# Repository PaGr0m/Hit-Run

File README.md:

# Hit&Run

## Projects
* [Controller] --- устройство-приемник, обрабатывает приходящие сигналы, визуализирует фиксацию, оснащен таймером.
* [WeaponSender] --- устройство-передатчик, фиксирует нажатие механической кнопки на наконечнике оружия и посылает сигнал на приемник.
* [RadioRemoteControl] --- пульт ДУ, для усправления контроллером.

[Controller]: <https://github.com/PaGr0m/Hit-Run/tree/master/Controller>
[WeaponSender]: <https://github.com/PaGr0m/Hit-Run/tree/master/WeaponSender>
[RadioRemoteControl]: <https://github.com/PaGr0m/Hit-Run/tree/master/RadioRemoteControl>

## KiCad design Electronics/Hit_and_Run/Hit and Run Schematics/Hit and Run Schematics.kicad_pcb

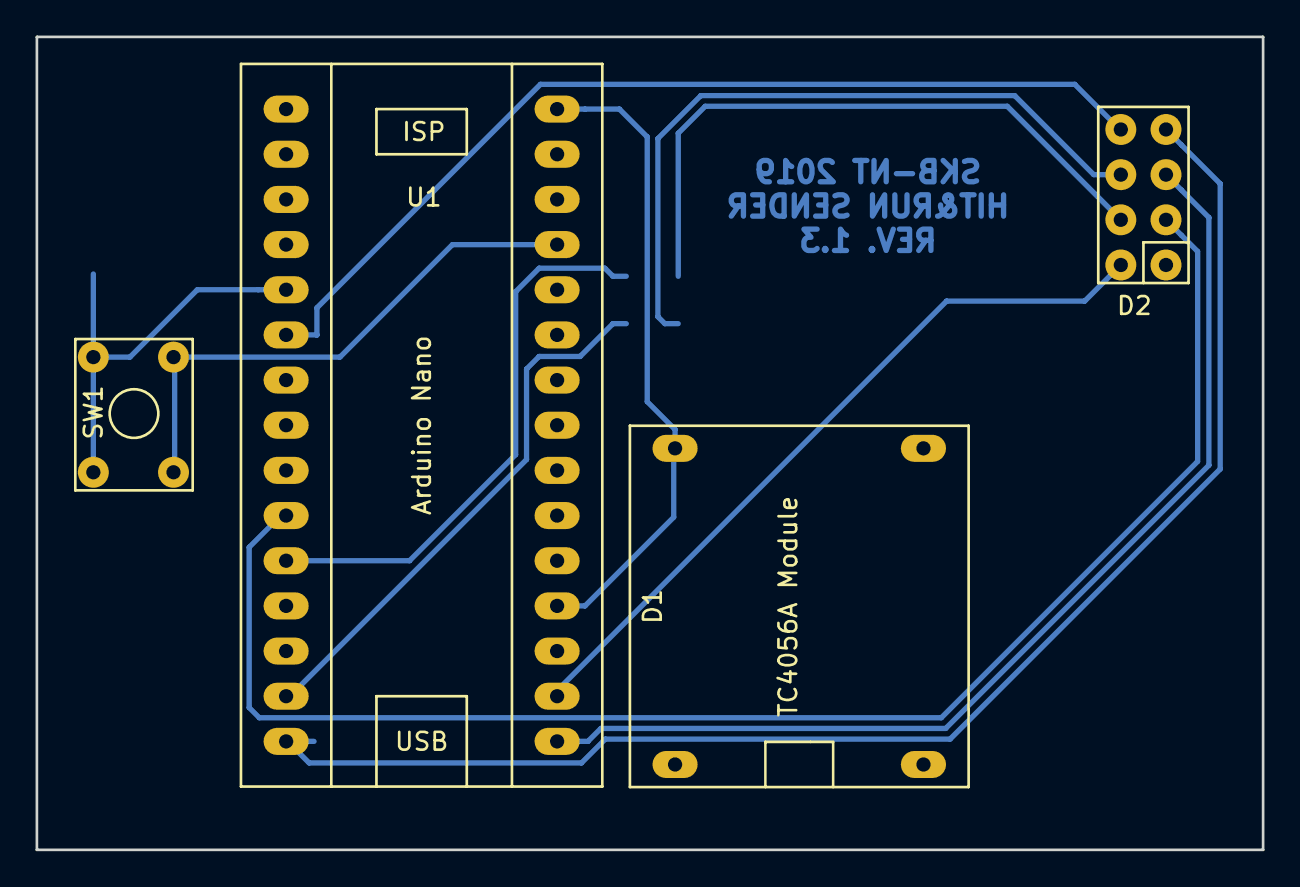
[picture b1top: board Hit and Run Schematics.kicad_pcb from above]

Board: 2 copper layers, 69.0 x 45.7 mm, 5 parts (0 on the bottom side), 11 nets.

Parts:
D1: TC4056A Module; TC4056A_Battery_module
D2: nRF24L01
R1: Default_Resistor; SMD_Resistor_1206
SW1: THT_Tactical_Button_6x6x3.5mm; THT_Tactical_Switch_6x6x3.5
U1: Arduino_Nano

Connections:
+3V3: D2.8, U1.17
+5V: SW1.2, U1.27
+BATT: D1.4, U1.19, U1.30
-BATT: D1.3, D2.1, R1.1, U1.29
unnamed: D2.2, U1.10
unnamed: D2.3, U1.16
unnamed: D2.4, U1.15
unnamed: D2.5, U1.6
unnamed: D2.6, U1.14
unnamed: D2.7, U1.11
unnamed: R1.2, SW1.1, U1.5

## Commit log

2019-02-14 Add some files
    Just program epee button. Test RF24 connection
2019-02-18 Separate Sender and Receiver
2019-02-19 Add Buzzer, Light-emitting diode
2019-02-20 Test SenderX2
2019-02-21 Complete Sender X2. Add Liquid Display
2019-02-25 Try RTC module
2019-02-25 Anything binary code
2019-04-16 Test code
2019-05-13 Working state
2019-05-14 Project Reborn
2019-05-15 Sender + Receiver + Controller
2019-05-17 IR remote control
2019-05-29 Test Interrupt NRF
2019-06-02 Test 2
2019-06-02 Test 3
2019-06-02 Hit&Run | Version 2.1
2019-06-03 Cleaning
2019-06-03 Cleaning
    Delete extra files
2019-06-03 Update .gitignore and delete extra files
2019-06-04 Test RadioRemoteControl
    Тестирование фичи. Следует проверить работоспособность на 2 Sender'ах, подумать о переделывании прерывания
2019-06-05 Rework RadioRemoteControl. Add comments in WeaponSender
2019-06-05 Add RTC timer, complete RadioRemoteControl
2019-06-06 Upd readme
2019-06-10 Add logger, delete ex files
2019-06-18 Upd SKB image
2019-06-18 Upd readme | Add skb link
2019-06-24 Little change
2019-06-24 Added LED Matrix and Buzzer.
    Added serialSettings. Rework comments. Added extra features
2019-06-24 Revert "Feature/led matrix"
2019-06-24 Revert "Hit&Run | Version 2.2"
2019-06-29 Refactoring
2019-07-01 Check
